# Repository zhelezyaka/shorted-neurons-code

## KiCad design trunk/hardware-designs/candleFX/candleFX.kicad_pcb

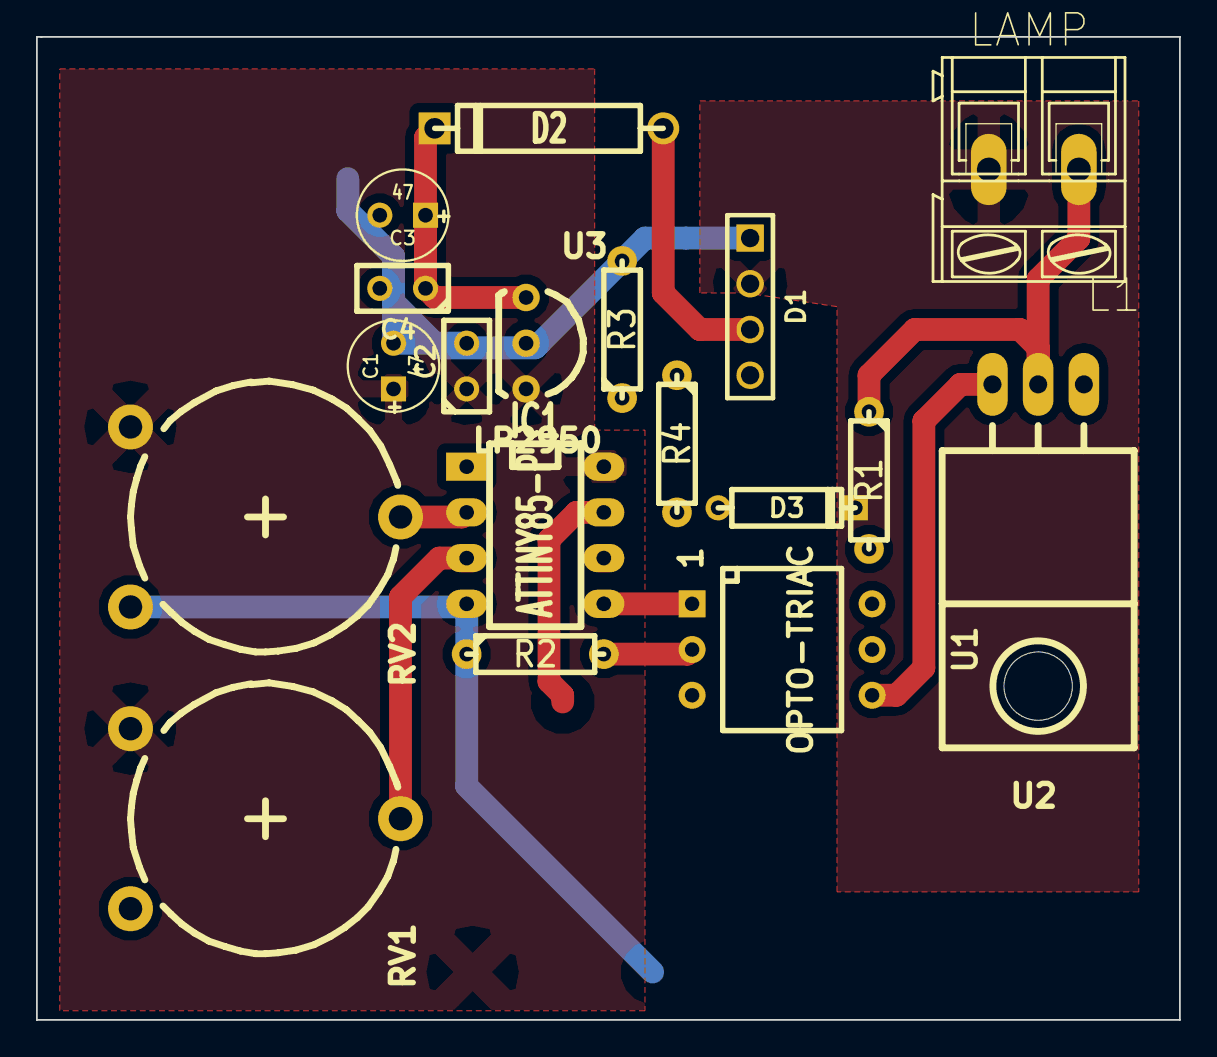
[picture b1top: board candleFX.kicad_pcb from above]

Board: 2 copper layers, 63.5 x 54.6 mm, 18 parts (0 on the bottom side), 14 nets.

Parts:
C1, C3: 47; C1V5
C2, C4: 0.1; C1
D1: BRIDGE; PIN_ARRAY_4x1
D2: DIODE; D5
D3: 1n4148; D3
IC1: ATTINY85-P; DIP-8__300_ELL
L1: LAMP; AK300-2
R1: 100; R3-LARGE_PADS
R2: 330; R3-LARGE_PADS
R3: 1k; R3-LARGE_PADS
R4: 10k; R3-LARGE_PADS
RV1, RV2: 20k; Potentiometer_Trimmer-Piher_PT15-V15_horizontal_RevA_02Aug2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
U1: OPTO-TRIAC; Optocoupler_6pin_wide_Stile-II_RevA_31Mar2011
U2: TRIAC; TO-220_Neutral123_Horizontal_LargePads
U3: LP2950; TO-92-Free-inline-wide

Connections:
+9V: C3.1, C4.1, D2.2, U3.1
+12V: D1.2, L1.2
-12V: D1.4, U2.1
GND: C1.2, C2.2, C3.2, C4.2, D1.1, D3.2, IC1.4, R2.1, R3.2, RV1.3, RV2.3, U3.2
unnamed: D1.3, D2.1, R4.1
unnamed: D3.1, IC1.7, R3.1, R4.2
unnamed: IC1.2, RV2.2
unnamed: IC1.3, RV1.2
unnamed: IC1.5, U1.1
unnamed: L1.1, R1.1, U2.2
unnamed: R1.2, U1.6
unnamed: R2.2, U1.2
unnamed: U1.4, U2.3
VCC: C1.1, C2.1, IC1.8, RV1.1, RV2.1, U3.3

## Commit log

2011-02-05 Initial directory structure.
2011-02-05 initial checkin try 4
2011-02-05 testing svn
2011-02-05 see if cpp syntax highlighting works
2011-02-05 add stuff from dad's
2011-02-05 removing test cpp file
2011-02-05 edits from Dads
2011-02-13 today
2011-02-21 yay! first library
2011-03-05 add config thingy, work out some clock bits
2011-03-09 added battery cutoff code, correct voltage reporting, cam working pretty good now.
2011-03-13 voltage ref, other fooling around
2011-03-14 1st stage of integrating anemometer/compass/temp thingy, stable though compass broken in this version
2011-03-15 bit of mods, this version went up in the tree on 20110314, hopefully working, anemometer bits disabled
2011-03-15 first attempt at very dim and night-blank display modes
2011-03-15 this version all brightnesses are synced
2011-04-19 refactor of clock in progress, changed name, tired of versions now that i have subversions :)
2011-04-28 april27
2011-05-01 seems to work fine on 35-bit, and should on flowerclock too. cross fingers!
2011-05-01 working with time zone DST buttons now and EEPROM config save. i think this version will make it to Heidi
2011-05-01 more
2011-05-01 better serial output
2011-05-09 progress?
2011-06-26 crash launcher initial dirs
2011-06-26 kill bad dir
2011-06-26 spacing change
2011-06-26 remove
2011-06-26 Add docs
2011-06-26 Add control_leds
2011-07-02 july 1 session at kevin's. "reciever" works
2011-07-03 control and receive programs w/2 channels
2011-07-06 added pins documentation
2011-07-08 updated pin layout docs
2011-07-14 added channel docs
2011-07-14 fixed layout a bit, added firing LED and HV sense divider
2011-07-14 oops, forgot to hit save with .sch
2011-07-14 - renamed since i realized that schematic is multi-page. - realized that we are switching ground, not HV, moved darlington to accomodate - fixed firing LED so that it will not shine when ignitor is o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
2011-07-16 demonstrator with basic rackside continuity and controller safety key
2011-07-17 documentation updates from working session on Fri Jul 15
2011-07-25 added comments
2011-07-25 changed battery sense location
2011-07-27 - renamed due to one file per page in gEDA - added RFM12b symbol
2011-07-27 rearranging
2011-07-27 -fix gafrc so that lib name of symbols makes sense
2011-07-27 - i think i have this core 90% done
2011-07-29 Update controle schematic
2011-07-29 - moved buzzer to pin D9, safety switch to D3. helps with PWM timer issue conflicting with interrupts - spacing for clarity in diagram
2011-07-31 - added 3.3V regulators - power caps - decoupling caps - fixed ICSP header to 6 pin and labelled it - added current shunt op amp - rack unit core may now be complete
2011-07-31 - fixed caps on wrong side of regulator
2011-08-06 more docs... yeehaw
2011-08-07 add rack unit main loop flow
2011-08-07 fixed odd misplacements
2011-08-07 updates from saturday working session with Kevin. mostly fixed caps and placement of buzzer
2011-08-15 first attempt at kicad commit
2011-08-15 - finished header connections - added LDO and caps - added battery and sense resistors - moved things around for clarity - now almost passes DRC check... antenna and ICSP 3.3V are only complaints
2011-08-25 - broke out into multi-sheet diagram - completed first draft of rackunit - added symbol for TSC888
2011-08-25 forgot to save master project file at same time as rest
2011-10-03 Schematic update
2011-10-28 First basically functional controller and rack unit code
2011-10-31 Fix off by 1 bugs for channel 4
2011-11-19 update pin mappings
2012-02-01 lib adds
2012-02-01 first try with forked kicad bits
2012-02-21 module and library sillytime
2012-06-09 first REAL shot at PCB
2012-06-10 second try at PCB layout. this one might actually work!
2012-06-11 further refined PCB, it has safety switch and fire switch and lots of errors fixed!
2012-06-12 pcb version 0.3. fixed inductor footprints, RSHUNT1, and made lots of power traces wider
2012-06-15 first good attempt at module PCB
2012-06-15 second shot at module PCB
2012-06-20 fixed whitespace. SOME PEOPLES CHILDREN... Jon. oh wait thats me too.
2012-06-29 rounded corners on PCB zones, removed VDD rectangle, other suggestions from sgrace
2012-07-07 rounded corners, plopped in a few missing caps on gpios and adc
2012-08-11 lots of revs, breakout board
2012-08-11 fixed libs and modules
2012-08-12 omgoodness... lots of updates, and submitted big panel for manufacturing
2012-10-20 check in because i should...
2013-01-26 bad bryan has not been checking in often
2013-02-02 who knows... about to add TMP101 and humidity sensor
2013-02-03 seems to work well with new 1/2 wave whip antennae. next will be optimizing response of arming buttons.
2013-02-10 working with reg71050 charge pump and solar, humidity, ds18b20, and tmp101, draws 300uA when idle.
2013-09-01 junk
2013-11-03 improvements to controller responsiveness
2013-11-10 catchup
2013-11-12 new radio fun
2013-11-28 rf22
2013-11-29 rf22 now working two way, also old 35 bit clock that never got committed
2014-01-04 check in before adding rfm69hw support
2014-03-02 change to 1.0.5 compatibility
2014-04-18 update pin stuff to match manufactured board
2014-08-10 try to get back in sync
2014-08-10 fixy
2014-08-10 fraking thing
2014-08-10 catcup from dads house
2014-08-10 crap
2014-08-10 worky?
2014-08-10 do it damnit
2014-08-10 end of this crap maybe
2014-08-10 why wont this sync
2014-08-10 craptastic
2014-08-13 time for a real radio library!
2014-08-14 compiles now with RadioHead! (unsure if anything works!)
2014-10-22 today!
2014-12-30 looking good, includes dimmer control pot
2015-01-09 test commit some crap adds
2015-11-02 Migrating wiki contents from Google Code
